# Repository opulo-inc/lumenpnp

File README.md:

# LumenPnP

The LumenPnP is an open source [pick and place machine](https://en.wikipedia.org/wiki/Pick-and-place_machine) that reliably and accurately assembles electronic components onto circuit boards.

The LumenPnP is available for sale on the [Opulo Website](https://www.opulo.io/products/lumenpnp). Machines are being used in active production daily. If you build or buy one, please help the project by documenting bugs with a GitHub issue.

**Please [read the wiki here](https://github.com/opulo-inc/lumenpnp/wiki)!** The wiki covers information about the state of the project, contributing instructions, and frequently asked questions.

Along with the pick and place machine itself, the project also includes feeders designed to work with the machine. The source for powered feeders can be found [in their separate repository](https://github.com/opulo-inc/feeder).

For exported versions of the source (STLs, schematic PDFs, compiled binaries, etc), you can find them attached to the [latest release](https://github.com/opulo-inc/lumenpnp/releases).

The LumenPnP's development process is being cataloged in a series of videos. A playlist of these can be found [here](https://www.youtube.com/playlist?list=PLIeJXmcg1baLBz3x0nCDqkYpKs2IWGHk4).

## How do I get one?

You can buy a machine on the [Opulo Website](https://www.opulo.io/products/lumenpnp)!

## Contributing

If you would like to contribute to the project, awesome! Check out the [contributing page](https://github.com/opulo-inc/lumenpnp/wiki/Contributing) to get started.

## Community

Discussion about the project happens on the [LumenPnP Discord server](https://discordapp.com/invite/TCwy6De)!

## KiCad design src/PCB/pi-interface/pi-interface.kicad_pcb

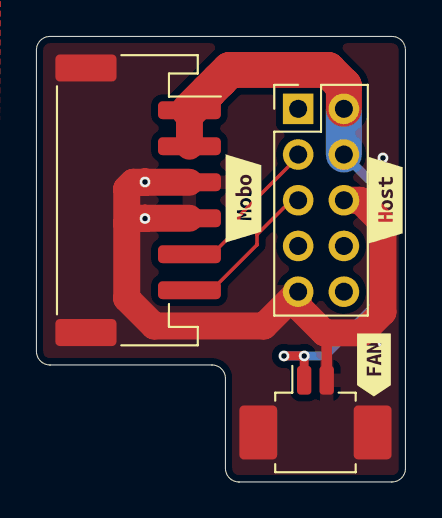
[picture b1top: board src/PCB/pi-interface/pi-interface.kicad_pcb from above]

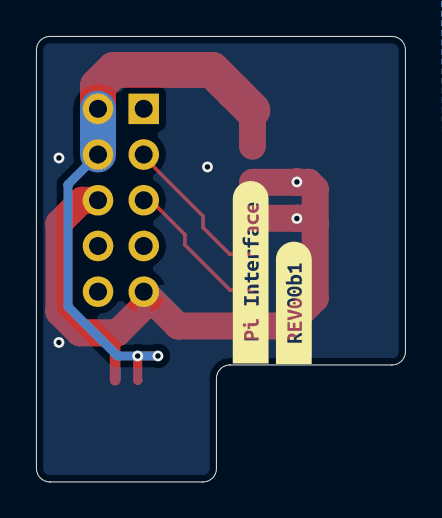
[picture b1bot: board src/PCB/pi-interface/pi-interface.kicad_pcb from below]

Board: 2 copper layers, 20.5 x 24.8 mm, 8 parts (2 on the bottom side), 4 nets.

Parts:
J1: PI; PinHeader_2x05_P2.54mm_Vertical
J2: MOBO; JST_PH_S6B-PH-SM4-TB_1x06-1MP_P2.00mm_Horizontal
J3: Conn_01x02_Pin; Molex_PicoBlade_53261-0271_1x02-1MP_P1.25mm_Horizontal
kibuzzard-6ABE9D80: G***; kibuzzard-6ABE9D80
kibuzzard-6ABE9DFF: G***; kibuzzard-6ABE9DFF
kibuzzard-6ABE9E4D: G***; kibuzzard-6ABE9E4D
kibuzzard-6ABE9E31: G***; kibuzzard-6ABE9E31
kibuzzard-6ABE9EAF: G***; kibuzzard-6ABE9EAF

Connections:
+5V: J1.2, J1.4, J2.1, J2.2, J3.1
BOOT: J1.3, J2.5
GND: J1.6, J1.9, J2.3, J2.4, J2.MP (MountPin), J3.2, J3.MP
RESET: J1.5, J2.6

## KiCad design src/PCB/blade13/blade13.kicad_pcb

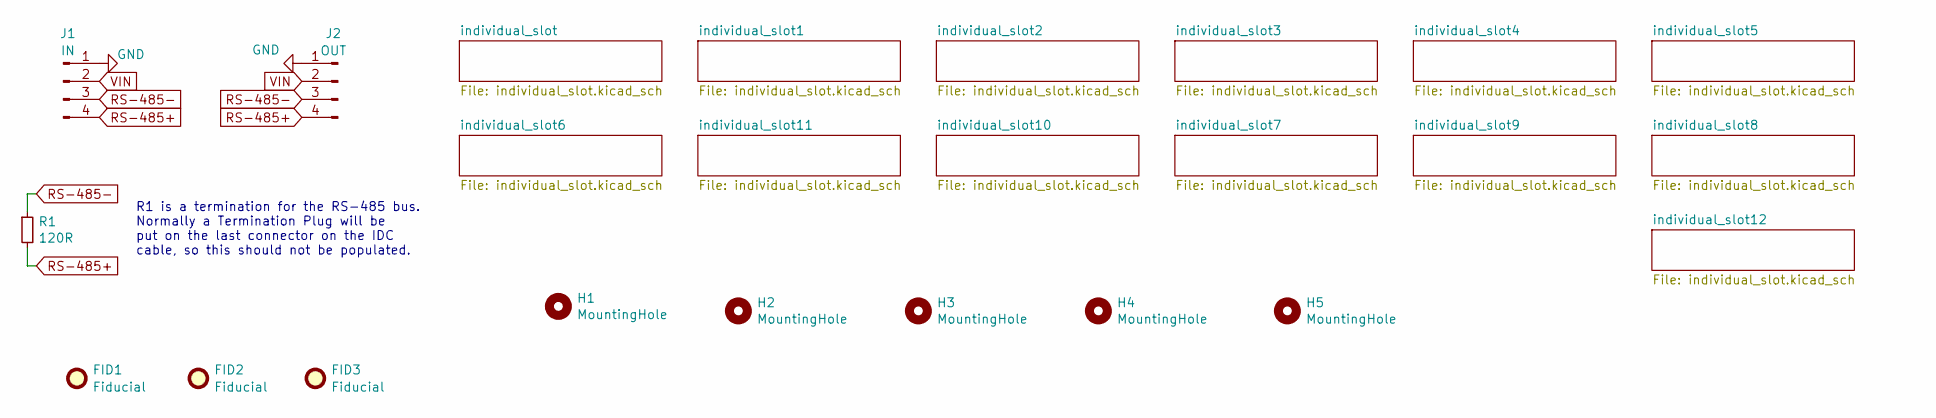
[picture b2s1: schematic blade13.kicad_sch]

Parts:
FID1, FID2, FID3: Fiducial; Fiducial_1mm_Mask2mm
H1, H2, H3, H4, H5: MountingHole; MountingHole_3.2mm_M3
J1: IN; JST_PH_B4B-PH-SM4-TB_1x04-1MP_P2.00mm_Vertical
J2: OUT; JST_PH_B4B-PH-SM4-TB_1x04-1MP_P2.00mm_Vertical
R1: 120R; R_0805_2012Metric; JLCPCB C17437

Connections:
GND: J1.1, J1.MP, J2.1, J2.MP; also elsewhere on the board
RS-485+: J1.4, J2.4, R1.2; also elsewhere on the board
RS-485-: J1.3, J2.3, R1.1; also elsewhere on the board
VIN: J1.2, J2.2; also elsewhere on the board

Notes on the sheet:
R1 is a termination for the RS-485 bus. Normally a Termination Plug will be put on the last connector on the IDC cable, so this should not be populated.

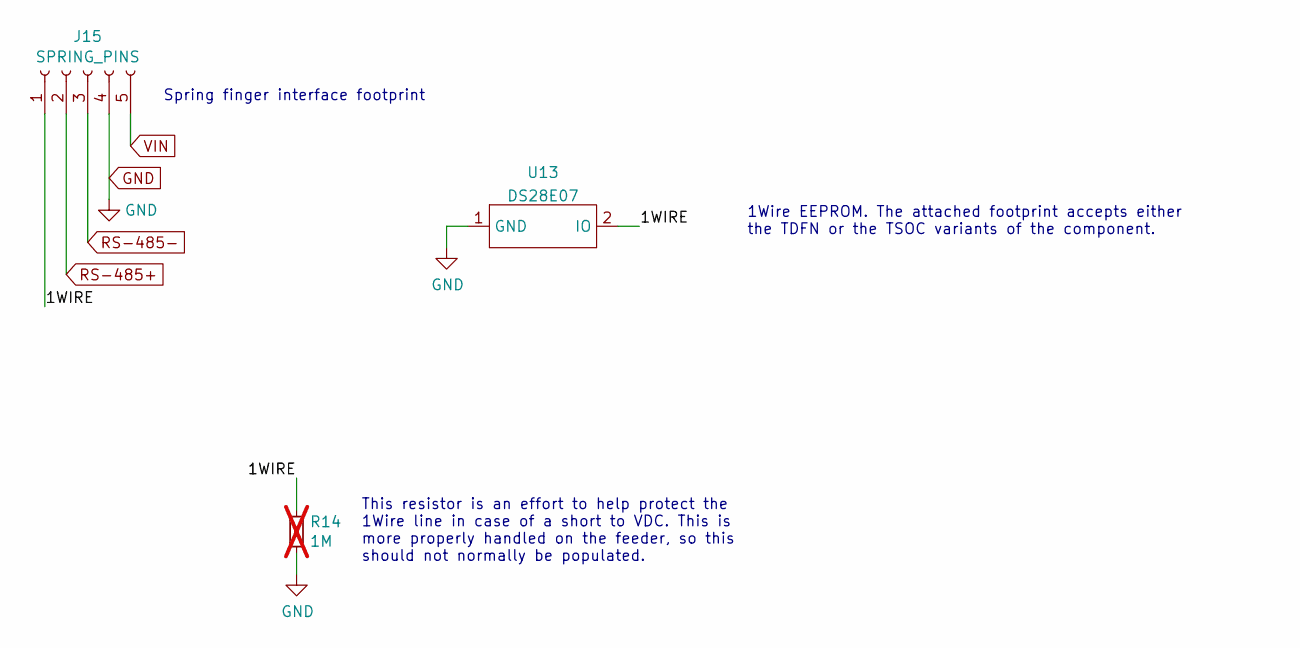
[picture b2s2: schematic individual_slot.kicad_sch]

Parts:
J15: SPRING_PINS; AVX-915-005-541-Contact-Surface
R14: 1M; R_0805_2012Metric; JLCPCB C17437; not fitted
U13: DS28E07; DS28E07_MULTI

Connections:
/individual_slot12/1WIRE: J15.1, R14.1, U13.2 (IO)
GND: J15.4, R14.2, U13.1 (GND); also elsewhere on the board
RS-485+: J15.2; also elsewhere on the board
RS-485-: J15.3; also elsewhere on the board
VIN: J15.5; also elsewhere on the board

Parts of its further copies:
J3, J4, J5, J6, J7, J8, J9, J10, J11, J12, J13, J14: SPRING_PINS; AVX-915-005-541-Contact-Surface
R2, R3, R4, R5, R6, R7, R8, R9, R10, R11, R12, R13: 1M; R_0805_2012Metric; JLCPCB C17437; not fitted
U1, U2, U3, U4, U5, U6, U7, U8, U9, U10, U11, U12: DS28E07; DS28E07_MULTI

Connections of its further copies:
/individual_slot1/1WIRE: J4.1, R3.1, U2.2 (IO)
/individual_slot2/1WIRE: J5.1, R4.1, U3.2 (IO)
/individual_slot3/1WIRE: J6.1, R5.1, U4.2 (IO)
/individual_slot4/1WIRE: J7.1, R6.1, U5.2 (IO)
/individual_slot5/1WIRE: J8.1, R7.1, U6.2 (IO)
/individual_slot6/1WIRE: J9.1, R8.1, U7.2 (IO)
/individual_slot7/1WIRE: J10.1, R9.1, U8.2 (IO)
/individual_slot8/1WIRE: J11.1, R10.1, U9.2 (IO)
/individual_slot9/1WIRE: J12.1, R11.1, U10.2 (IO)
/individual_slot10/1WIRE: J13.1, R12.1, U11.2 (IO)
/individual_slot11/1WIRE: J14.1, R13.1, U12.2 (IO)
/individual_slot/1WIRE: J3.1, R2.1, U1.2 (IO)
GND: J3.4, J4.4, J5.4, J6.4, J7.4, J8.4, J9.4, J10.4, J11.4, J12.4, J13.4, J14.4, R2.2, R3.2, R4.2, R5.2, R6.2, R7.2, R8.2, R9.2, R10.2, R11.2, R12.2, R13.2, U1.1 (GND), U2.1 (GND), U3.1 (GND), U4.1 (GND), U5.1 (GND), U6.1 (GND), U7.1 (GND), U8.1 (GND), U9.1 (GND), U10.1 (GND), U11.1 (GND), U12.1 (GND); also elsewhere on the board
RS-485+: J3.2, J4.2, J5.2, J6.2, J7.2, J8.2, J9.2, J10.2, J11.2, J12.2, J13.2, J14.2; also elsewhere on the board
RS-485-: J3.3, J4.3, J5.3, J6.3, J7.3, J8.3, J9.3, J10.3, J11.3, J12.3, J13.3, J14.3; also elsewhere on the board
VIN: J3.5, J4.5, J5.5, J6.5, J7.5, J8.5, J9.5, J10.5, J11.5, J12.5, J13.5, J14.5; also elsewhere on the board

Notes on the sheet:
This resistor is an effort to help protect the 1Wire line in case of a short to VDC. This is more properly handled on the feeder, so this should not normally be populated.
Spring finger interface footprint
1Wire EEPROM. The attached footprint accepts either the TDFN or the TSOC variants of the component.

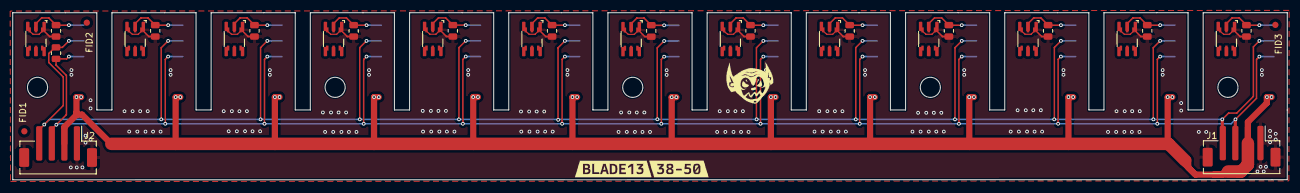
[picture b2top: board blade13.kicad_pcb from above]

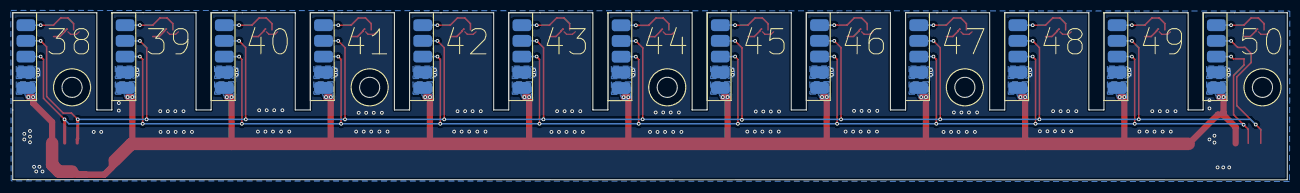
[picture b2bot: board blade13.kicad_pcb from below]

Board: 2 copper layers, 203.0 x 26.6 mm, 53 parts (13 on the bottom side), 17 nets.

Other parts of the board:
kibuzzard-65FDDA45: G***; kibuzzard-65FDDA45
kibuzzard-65FDDA59: G***; kibuzzard-65FDDA59
kibuzzard-65FDDA61: G***; kibuzzard-65FDDA61

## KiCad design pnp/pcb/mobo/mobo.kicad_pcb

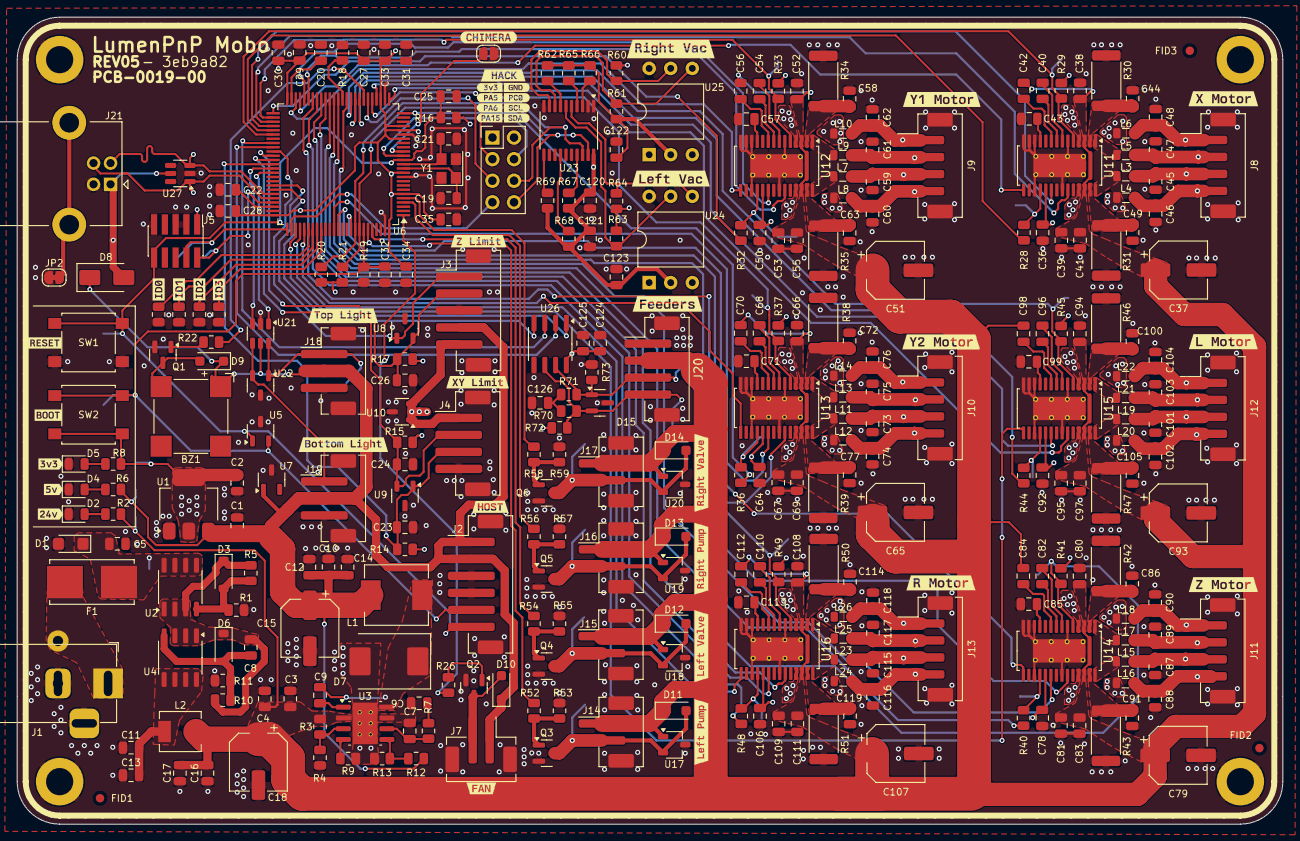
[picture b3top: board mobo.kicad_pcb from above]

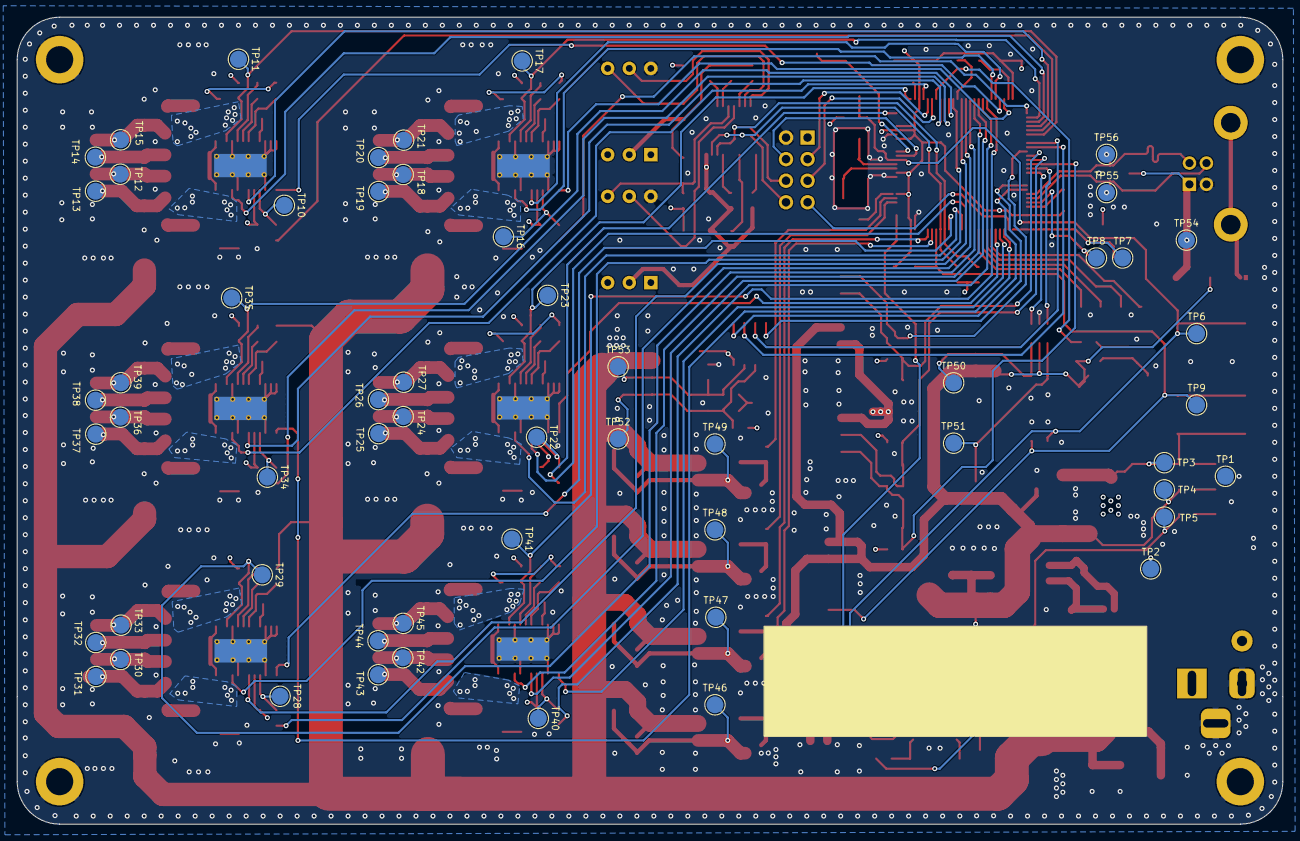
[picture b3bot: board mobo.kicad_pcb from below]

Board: 4 copper layers, 149.0 x 95.0 mm, 404 parts (57 on the bottom side), 207 nets.

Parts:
BZ1: Buzzer; MagneticBuzzer_CUI_CMT-8504-100-SMT
C1, C2, C3, C4, C5, C10, C11, C12, C13, C14, C16, C17, C38, C52, C66, C80, C94, C108, C121: 10u; C_0805_2012Metric
C6: 4.7n; C_0805_2012Metric
C7: 47p; C_0805_2012Metric
C8, C9, C23, C24, C25, C26, C29, C30, C31, C32, C33, C34, C35, C36, C39, C41, C42, C44, C49, C50, C53, C55, C56, C58, C63, C64, C67, C69, C70, C72, C77, C78, C81, C83, C84, C86, C91, C92, C95, C97, C98, C100, C105, C106, C109, C111, C112, C114, C119, C120, C122, C123, C124, C125, C126: 100n; C_0805_2012Metric
C15, C18, C37, C51, C65, C79, C93, C107: 100u; CP_Elec_6.3x7.7
C19, C21: 10p; C_0805_2012Metric
C20, C22, C27, C28: 2.2u; C_0805_2012Metric
C40, C54, C68, C82, C96, C110: 22n; C_0805_2012Metric
C43, C57, C71, C85, C99, C113: 4.7u; C_0805_2012Metric
C45, C46, C47, C48, C59, C60, C61, C62, C73, C74, C75, C76, C87, C88, C89, C90, C101, C102, C103, C104, C115, C116, C117, C118: 470p; C_0805_2012Metric
D1: SMF28A; D_SMF
D2, D4, D5: Green; LED_0805_2012Metric
D3, D6: BZT52C16; D_SOD-123
D7: B560C; D_SMC
D8: SS34; D_SMA
D9, D10, D11, D12, D13, D14: SM4007; D_SOD-123F
D15: SM712_SOT23; SOT-23
F1: Fuse; Fuseholder_Littelfuse_Nano2_154x
FID1, FID2, FID3: Fiducial; Fiducial_1mm_Mask2mm
G1: Opulo-Logo; logo_mask
G2: Goblin-logo; goblin
H1, H2, H3, H4: MountingHole_Pad; MountingHole_3.2mm_M3_DIN965_Pad
J1: COMBO_POWER_JACK; BarrelJack_Horizontal
J2: HOST; JST_PH_B6B-PH-SM4-TB_1x06-1MP_P2.00mm_Vertical
J3: Z_LIMIT; JST_PH_B5B-PH-SM4-TB_1x05-1MP_P2.00mm_Vertical
J4: XY_LIMIT; JST_PH_B4B-PH-SM4-TB_1x04-1MP_P2.00mm_Vertical
J5: SWD Header; PinHeader_2x05_P1.27mm_Vertical_SMD
J6: HACK_HEADER; PinHeader_2x04_P2.54mm_Vertical
J7: FAN; JST_PH_B2B-PH-SM4-TB_1x02-1MP_P2.00mm_Vertical
J8, J9, J10, J11, J12, J13: MOTOR; JST_PH_B4B-PH-SM4-TB_1x04-1MP_P2.00mm_Vertical
J14, J15, J16, J17: FET; JST_PH_B2B-PH-SM4-TB_1x02-1MP_P2.00mm_Vertical
J18: TOP_LIGHT; JST_PH_B3B-PH-SM4-TB_1x03-1MP_P2.00mm_Vertical
J19: BTM_LIGHT; JST_PH_B3B-PH-SM4-TB_1x03-1MP_P2.00mm_Vertical
J20: FEEDERS; JST_PH_B4B-PH-SM4-TB_1x04-1MP_P2.00mm_Vertical
J21: USB_B; USB_B_Lumberg_2411_02_Horizontal
JP1: CHIMERA_JUMPER; SolderJumper-2_P1.3mm_Open_RoundedPad1.0x1.5mm
JP2: SHIELD_GND; SolderJumper-2_P1.3mm_Bridged_RoundedPad1.0x1.5mm
L1: 8.2uH; L_Sunlord_MWSA0603S
L2: 2.2u; L_Sunlord_MWSA0402S
L3, L4, L5, L6, L7, L8, L9, L10, L11, L12, L13, L14, L15, L16, L17, L18, L19, L20, L21, L22, L23, L24, L25, L26: L_Ferrite; L_0805_2012Metric
Q1, Q2, Q3, Q4, Q5, Q6: AO3400A; SOT-23
R1, R2, R3, R11, R13, R14, R15, R16, R17, R18, R19, R29, R33, R37, R41, R45, R49, R53, R55, R57, R59, R62, R65, R66, R67, R68, R69: 10k; R_0805_2012Metric
R4, R5, R6, R10, R20, R21, R60, R61, R63, R64: 4.7k; R_0805_2012Metric
R7: 16.9k; R_0805_2012Metric
R8, R22, R26, R28, R32, R36, R40, R44, R48, R52, R54, R56, R58: 1k; R_0805_2012Metric
R9: 243k; R_0805_2012Metric
R12: 53.6k; R_0805_2012Metric
R23, R24, R25, R27: 0R; R_0805_2012Metric
R30, R31, R34, R35, R38, R39, R42, R43, R46, R47, R50, R51: 120m; R_2512_6332Metric
R70, R71: 60.4; R_0805_2012Metric
R72, R73: 330; R_0805_2012Metric
SW1, SW2: SW_Push; SW_SPST_B3S-1000
TP1, TP2, TP3, TP4, TP5, TP6, TP7, TP8, TP9, TP10, TP11, TP12, TP13, TP14, TP15, TP16, TP17, TP18, TP19, TP20, TP21, TP22, TP23, TP24, TP25, TP26, TP27, TP28, TP29, TP30, TP31, TP32, TP33, TP34, TP35, TP36, TP37, TP38, TP39, TP40, TP41, TP42, TP43, TP44, TP45, TP46, TP47, TP48, TP49, TP50, TP51, TP52, TP53, TP54, TP55, TP56: TestPoint; TestPoint_Pad_D2.0mm
U1: AP1117-33; SOT-223-3_TabPin2
U2, U4: FDS4435BZ; SO-8_3.9x4.9mm_P1.27mm
U3: TPS54560BDDA; Texas_R-PDSO-G8_EP2.95x4.9mm_Mask2.4x3.1mm_ThermalVias
U5, U8, U9, U10: PESD3V3S2UT; SOT-23-3
U6: STM32F407VETx; LQFP-100_14x14mm_P0.5mm
U7, U22: PESD5V2S2UT; SOT-23-3
U11, U12, U13, U14, U15, U16: TMC2226-SA; HTSSOP-28-1EP_4.4x9.7mm_P0.65mm_EP2.75x6.2mm_ThermalVias
U17, U18, U19, U20: PESD24BS3; TSOT-23
U21: SN74LVC2G34; SOT-23-6
U23: PCA9545A; TSSOP-20_4.4x6.5mm_P0.65mm
U24, U25: XGZP6857D; DIP-6_W10.16mm
U26: THVD1400D; SOIC-8_3.9x4.9mm_P1.27mm
U27: SRV05-4; SOT-23-6
Y1: 8MHz; Crystal_SMD_3225-4Pin_3.2x2.5mm
kibuzzard-65DCF286: G***; kibuzzard-65DCF286
kibuzzard-65E24FAE: G***; kibuzzard-65E24FAE
kibuzzard-65E215D8: G***; kibuzzard-65E215D8
kibuzzard-65E215EC: G***; kibuzzard-65E215EC
kibuzzard-65E240B2: G***; kibuzzard-65E240B2
kibuzzard-65E241C9: G***; kibuzzard-65E241C9
kibuzzard-65E2151D: G***; kibuzzard-65E2151D
kibuzzard-65E2155B: G***; kibuzzard-65E2155B
kibuzzard-65E2156F: G***; kibuzzard-65E2156F
kibuzzard-65E2408C: G***; kibuzzard-65E2408C
kibuzzard-65E2409D: G***; kibuzzard-65E2409D
kibuzzard-65E2504F: G***; kibuzzard-65E2504F
kibuzzard-65E24108: G***; kibuzzard-65E24108
kibuzzard-65E24112: G***; kibuzzard-65E24112
kibuzzard-65E24141: G***; kibuzzard-65E24141
kibuzzard-65E25035: G***; kibuzzard-65E25035
kibuzzard-65E25071: G***; kibuzzard-65E25071
kibuzzard-65F1FEA3: G***; kibuzzard-65F1FEA3
kibuzzard-6585C0AF: G***; kibuzzard-6585C0AF
kibuzzard-6585C0D3: G***; kibuzzard-6585C0D3
kibuzzard-6585C08F: G***; kibuzzard-6585C08F
kibuzzard-6585C058: G***; kibuzzard-6585C058
kibuzzard-6606EA2E: G***; kibuzzard-6606EA2E
kibuzzard-6606EA4F: G***; kibuzzard-6606EA4F
kibuzzard-6606EA6E: G***; kibuzzard-6606EA6E
kibuzzard-65709CC6: G***; kibuzzard-65709CC6
kibuzzard-65709E62: G***; kibuzzard-65709E62
kibuzzard-65848E86: G***; kibuzzard-65848E86
kibuzzard-65848E91: G***; kibuzzard-65848E91
kibuzzard-65848EB6: G***; kibuzzard-65848EB6
kibuzzard-65848FCC: G***; kibuzzard-65848FCC
kibuzzard-65848FD5: G***; kibuzzard-65848FD5
kibuzzard-65848FDC: G***; kibuzzard-65848FDC
kibuzzard-65848FE3: G***; kibuzzard-65848FE3
kibuzzard-65848FE9: G***; kibuzzard-65848FE9
kibuzzard-65848FEF: G***; kibuzzard-65848FEF
kibuzzard-660711AC: G***; kibuzzard-660711AC
kibuzzard-66071149: G***; kibuzzard-66071149

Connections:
+3.3V: C2.1, C27.1, C28.1, C29.1, C30.1, C31.1, C33.1, C34.1, C35.1, C36.2, C50.2, C64.2, C78.2, C92.2, C106.2, C120.1, C121.1, C122.1, C123.1, C124.1, C125.1, J3.5, J4.1, J5.1 (VTref), J6.1, R8.1, R14.2, R15.2, R16.1, R17.2, R20.1, R21.1, R29.1, R33.1, R37.1, R41.1, R45.1, R49.1, R60.2, R61.2, R62.1, R63.1, R64.1, R65.1, R66.1, R67.2, R68.2, R69.2, R72.1, SW2.2, TP3.1 (1_1), U1.2 (VO), U6.6 (VBAT), U6.11 (VDD), U6.19 (VDD), U6.21 (VREF+), U6.22 (VDDA), U6.28 (VDD), U6.50 (VDD), U6.75 (VDD), U6.100 (VDD), U10.1, U10.2, U11.19 (VCC_IO), U12.19 (VCC_IO), U13.19 (VCC_IO), U14.19 (VCC_IO), U15.19 (VCC_IO), U16.19 (VCC_IO), U23.20 (VDD), U24.2 (VDD), U25.2 (VDD), U26.8 (VCC)
+5V: BZ1.1 (-), C1.1, C10.2, C12.2, C14.2, C15.1, D8.1 (K), D9.1 (K), D10.1 (K), J2.1, J2.2, J3.4, J7.1, J18.2, J19.2, L1.2, R6.1, R12.1, TP4.1 (1_1), U1.3 (VI), U7.1, U21.5 (VCC)
/Lighting/BTM_LIGHT: U6.64 (PC7), U21.3 (2A)
/Microcontroller/AUX: J3.1, U6.60 (PD13), U8.1
/Microcontroller/BOOT1: R18.1, U6.37 (PB2)
/Microcontroller/BUZZER: R22.1, U6.32 (PA7)
/Microcontroller/CHIMERA: JP1.1 (A), U6.16 (PC1)
/Microcontroller/FAN: R26.1, U6.1 (PE2)
/Microcontroller/I2C_SCL: J6.6, R20.2, U6.92 (PB6), U23.18 (SCL)
/Microcontroller/I2C_SDA: J6.8, R21.2, U6.93 (PB7), U23.19 (SDA)
/Microcontroller/ID0: R23.2, U6.81 (PD0)
/Microcontroller/ID1: R24.2, U6.82 (PD1)
/Microcontroller/ID2: R25.2, U6.83 (PD2)
/Microcontroller/ID3: R27.2, U6.84 (PD3)
/Microcontroller/LUMEN_AUX_A1: J6.4, U6.15 (PC0)
/Microcontroller/LUMEN_AUX_PWM1: J6.3, U6.30 (PA5)
/Microcontroller/LUMEN_AUX_PWM2: J6.5, U6.31 (PA6)
/Microcontroller/LUMEN_AUX_PWM3: J6.7, U6.77 (PA15)
/Microcontroller/MOS1: R52.2, U6.95 (PB8)
/Microcontroller/MOS2: R54.2, U6.96 (PB9)
/Microcontroller/MOS3: R56.2, U6.4 (PE5)
/Microcontroller/MOS4: R58.2, U6.5 (PE6)
/Microcontroller/PA2: R36.2, U6.25 (PA2)
/Microcontroller/PA3: R37.2, TP23.1 (1_1), U6.26 (PA3), U13.5 (~EN)
/Microcontroller/PA4: U6.29 (PA4), U15.23 (DIR)
/Microcontroller/PB0: R45.2, TP35.1 (1_1), U6.35 (PB0), U15.5 (~EN)
/Microcontroller/PB1: U6.36 (PB1), U14.23 (DIR)
/Microcontroller/PB5: U6.91 (PB5), U14.15 (DIAG)
/Microcontroller/PB10: U6.47 (PB10), U11.15 (DIAG)
/Microcontroller/PB11: U6.48 (PB11), U12.15 (DIAG)
/Microcontroller/PB12: R32.2, U6.51 (PB12)
/Microcontroller/PB13: R33.2, TP17.1 (1_1), U6.52 (PB13), U12.5 (~EN)
/Microcontroller/PB14: U6.53 (PB14), U11.23 (DIR)
/Microcontroller/PB15: U6.54 (PB15), U11.20 (STEP)
/Microcontroller/PC4: U6.33 (PC4), U15.20 (STEP)
/Microcontroller/PC5: R44.2, U6.34 (PC5)
/Microcontroller/PC10: U6.78 (PC10), U15.15 (DIAG)
/Microcontroller/PC11: U6.79 (PC11), U16.15 (DIAG)
/Microcontroller/PC12: U6.80 (PC12), U13.15 (DIAG)
/Microcontroller/PD6: U6.87 (PD6), U13.20 (STEP)
/Microcontroller/PD7: U6.88 (PD7), U13.23 (DIR)
/Microcontroller/PD9: R29.2, TP11.1 (1_1), U6.56 (PD9), U11.5 (~EN)
/Microcontroller/PE7: U6.38 (PE7), U14.20 (STEP)
/Microcontroller/PE8: R40.2, U6.39 (PE8)
/Microcontroller/PE9: R41.2, TP29.1 (1_1), U6.40 (PE9), U14.5 (~EN)
/Microcontroller/PE10: U6.41 (PE10), U16.23 (DIR)
/Microcontroller/PE11: U6.42 (PE11), U16.20 (STEP)
/Microcontroller/PE12: R48.2, U6.43 (PE12)
/Microcontroller/PE13: R49.2, TP41.1 (1_1), U6.44 (PE13), U16.5 (~EN)
/Microcontroller/PE14: U6.45 (PE14), U12.23 (DIR)
/Microcontroller/PE15: U6.46 (PE15), U12.20 (STEP)
/Microcontroller/RS485_DE: U6.58 (PD11), U26.3 (DE)
/Microcontroller/RS485_RE: U6.59 (PD12), U26.2 (~RE)
/Microcontroller/RS485_RX: U6.69 (PA10), U26.1 (RO)
/Microcontroller/RS485_TX: U6.68 (PA9), U26.4 (DI)
/Microcontroller/SWCLK: J5.4 (SWDCLK/TCK), TP7.1 (1_1), U6.76 (PA14)
/Microcontroller/SWDIO: J5.2 (SWDIO/TMS), TP8.1 (1_1), U6.72 (PA13)
/Microcontroller/USB_D+: J21.3 (D+), TP55.1 (1_1), U6.71 (PA12), U27.1 (IO1)
/Microcontroller/USB_D-: J21.2 (D-), TP56.1 (1_1), U6.70 (PA11), U27.3 (IO2)
/Microcontroller/X_LIMIT: C23.1, J4.3, R14.1, U6.63 (PC6), U9.1
/Microcontroller/X_UART: R28.2, U6.55 (PD8)
/Microcontroller/Y_LIMIT: C24.1, J4.2, R15.1, U6.62 (PD15), U9.2
/Microcontroller/Z_LIMIT: C26.1, J3.2, R17.1, U6.61 (PD14), U8.2
/Motor L/5VOUT: C99.2, U15.11 (5VOUT)
/Motor L/A1: C101.2, J12.3, L19.2, TP36.1 (1_1)
/Motor L/A2: C102.1, J12.4, L20.2, TP37.1 (1_1)
/Motor L/B1: C103.2, J12.2, L21.2, TP38.1 (1_1)
/Motor L/B2: C104.1, J12.1, L22.2, TP39.1 (1_1)
/Motor R/5VOUT: C113.2, U16.11 (5VOUT)
/Motor R/A1: C115.2, J13.3, L23.2, TP42.1 (1_1)
/Motor R/A2: C116.1, J13.4, L24.2, TP43.1 (1_1)
/Motor R/B1: C117.2, J13.2, L25.2, TP44.1 (1_1)
/Motor R/B2: C118.1, J13.1, L26.2, TP45.1 (1_1)
/Motor X/5VOUT: C43.2, U11.11 (5VOUT)
/Motor X/A1: C45.2, J8.3, L3.2, TP12.1 (1_1)
/Motor X/A2: C46.1, J8.4, L4.2, TP13.1 (1_1)
/Motor X/B1: C47.2, J8.2, L5.2, TP14.1 (1_1)
/Motor X/B2: C48.1, J8.1, L6.2, TP15.1 (1_1)
/Motor Y1/5VOUT: C57.2, U12.11 (5VOUT)
/Motor Y1/A1: C59.2, J9.3, L7.2, TP18.1 (1_1)
/Motor Y1/A2: C60.1, J9.4, L8.2, TP19.1 (1_1)
/Motor Y1/B1: C61.2, J9.2, L9.2, TP20.1 (1_1)
/Motor Y1/B2: C62.1, J9.1, L10.2, TP21.1 (1_1)
/Motor Y2/5VOUT: C71.2, U13.11 (5VOUT)
/Motor Y2/A1: C73.2, J10.3, L11.2, TP24.1 (1_1)
/Motor Y2/A2: C74.1, J10.4, L12.2, TP25.1 (1_1)
/Motor Y2/B1: C75.2, J10.2, L13.2, TP26.1 (1_1)
/Motor Y2/B2: C76.1, J10.1, L14.2, TP27.1 (1_1)
/Motor Z/5VOUT: C85.2, U14.11 (5VOUT)
/Motor Z/A1: C87.2, J11.3, L15.2, TP30.1 (1_1)
/Motor Z/A2: C88.1, J11.4, L16.2, TP31.1 (1_1)
/Motor Z/B1: C89.2, J11.2, L17.2, TP32.1 (1_1)
/Motor Z/B2: C90.1, J11.1, L18.2, TP33.1 (1_1)
/Power/POWER_SUPPLY: F1.1, J1.1, J1.4
/Power/VIN: C5.2, D1.1 (A1), F1.2, TP2.1 (1_1), U2.5 (D), U2.6 (D), U2.7 (D), U2.8 (D)
/RS485/RS-485+: D15.2 (A2), J20.4, R70.1, R72.2, TP52.1 (1_1), U26.6 (A)
/RS485/RS-485-: D15.1 (A1), J20.3, R71.2, R73.1, TP53.1 (1_1), U26.7 (B)
/Vacuum sensors/SC0: R63.2, U23.6 (SC0), U24.5 (SCL)
/Vacuum sensors/SC1: R60.1, U23.9 (SC1), U25.5 (SCL)
/Vacuum sensors/SD0: R64.2, U23.5 (SD0), U24.4 (SDA)
/Vacuum sensors/SD1: R61.1, U23.8 (SD1), U25.4 (SDA)
BOOT: C32.1, J2.5, R19.1, SW2.1, TP9.1 (1_1), U5.2, U6.94 (BOOT0)
GND: C1.2, C2.2, C3.1, C4.1, C5.1, C6.1, C7.1, C10.1, C11.1, C12.1, C13.1, C14.1, C15.2, C16.1, C17.1, C18.2, C19.2, C20.2, C21.2, C22.2, C23.2, C24.2, C25.2, C26.2, C27.2, C28.2, C29.2, C30.2, C31.2, C32.2, C33.2, C34.2, C35.2, C36.1, C37.2, C38.1, C39.1, C41.1, C43.1, C44.1, C45.1, C46.2, C47.1, C48.2, C49.1, C50.1, C51.2, C52.1, C53.1, C55.1, C57.1, C58.1, C59.1, C60.2, C61.1, C62.2, C63.1, C64.1, C65.2, C66.1, C67.1, C69.1, C71.1, C72.1, C73.1, C74.2, C75.1, C76.2, C77.1, C78.1, C79.2, C80.1, C81.1, C83.1, C85.1, C86.1, C87.1, C88.2, C89.1, C90.2, C91.1, C92.1, C93.2, C94.1, C95.1, C97.1, C99.1, C100.1, C101.1, C102.2, C103.1, C104.2, C105.1, C106.1, C107.2, C108.1, C109.1, C111.1, C113.1, C114.1, C115.1, C116.2, C117.1, C118.2, C119.1, C120.2, C121.2, C122.2, C123.2, C124.2, C125.2, C126.1, D1.2 (A2), D2.1 (K), D4.1 (K), D5.1 (K), D7.2 (A), D15.3 (common), H1.1 (1_1), H2.1 (1_1), H3.1 (1_1), H4.1 (1_1), J1.2, J1.3, J2.3, J2.4, J2.MP (MountPin), J3.3, J3.MP (MountPin), J4.4, J4.MP (MountPin), J5.3 (GND), J5.5 (GND), J5.9 (GNDDetect), J6.2, J7.MP (MountPin), J8.MP (MountPin), J9.MP (MountPin), J10.MP (MountPin), J11.MP (MountPin), J12.MP (MountPin), J13.MP (MountPin), J14.MP (MountPin), J15.MP (MountPin), J16.MP (MountPin), J17.MP (MountPin), J18.3, J18.MP (MountPin), J19.3, J19.MP (MountPin), J20.1, J20.MP (MountPin), J21.4 (GND), JP1.2 (B), JP2.2 (B), Q1.2 (S), Q2.2 (S), Q3.2 (S), Q4.2 (S), Q5.2 (S), Q6.2 (S), R1.2, R4.2, R9.2, R11.2, R13.2, R18.2, R19.2, R23.1, R24.1, R25.1, R27.1, R30.2, R31.2, R34.2, R35.2, R38.2, R39.2, R42.2, R43.2, R46.2, R47.2, R50.2, R51.2, R53.1, R55.1, R57.1, R59.1, R73.2, SW1.1, TP1.1 (1_1), U1.1 (GND), U3.7 (GND), U3.9 (GND), U5.3, U6.10 (VSS), U6.20 (VSSA), U6.27 (VSS), U6.74 (VSS), U6.99 (VSS), U7.3, U8.3, U9.3, U10.3, U11.6 (GND), U11.12 (MS1_AD0), U11.13 (NC), U11.14 (MS2_AD1), U11.17 (CLK), U11.22 (GND), U11.29 (GND), U12.6 (GND), U12.12 (MS1_AD0), U12.13 (NC), U12.14 (MS2_AD1), U12.17 (CLK), U12.22 (GND), U12.29 (GND), U13.6 (GND), U13.12 (MS1_AD0), U13.13 (NC), U13.14 (MS2_AD1), U13.17 (CLK), U13.22 (GND), U13.29 (GND), U14.6 (GND), U14.12 (MS1_AD0), U14.13 (NC), U14.14 (MS2_AD1), U14.17 (CLK), U14.22 (GND), U14.29 (GND), U15.6 (GND), U15.12 (MS1_AD0), U15.13 (NC), U15.14 (MS2_AD1), U15.17 (CLK), U15.22 (GND), U15.29 (GND), U16.6 (GND), U16.12 (MS1_AD0), U16.13 (NC), U16.14 (MS2_AD1), U16.17 (CLK), U16.22 (GND), U16.29 (GND), U17.3, U18.3, U19.3, U20.3, U21.2 (GND), U22.3, U23.1 (A0), U23.2 (A1), U23.10 (VSS), U24.6 (GND), U25.6 (GND), U26.5 (GND), U27.2 (VN), Y1.2, Y1.4
unnamed: BZ1.2 (+), D9.2 (A), Q1.3 (D)
unnamed: C6.2, R7.2
unnamed: C11.2, C13.2, L2.1, U4.5 (D), U4.6 (D), U4.7 (D), U4.8 (D)
unnamed: C126.2, R70.2, R71.1
unnamed: D2.2 (A), R2.2
unnamed: D3.2 (A), R1.1, R5.2, U2.4 (G)
unnamed: C8.2, D3.1 (K), D6.1 (K), R5.1, R10.1, U2.1 (S), U2.2 (S), U2.3 (S), U4.1 (S), U4.2 (S), U4.3 (S)
unnamed: D4.2 (A), R6.2
unnamed: D5.2 (A), R8.2
unnamed: C8.1, D6.2 (A), R10.2, R11.1, U4.4 (G)
unnamed: C9.1, D7.1 (K), L1.1, U3.8 (SW)
unnamed: D10.2 (A), J7.2, Q2.3 (D)
unnamed: D11.2 (A), J14.2, Q3.3 (D), TP46.1 (1_1), U17.2
unnamed: D12.2 (A), J15.2, Q4.3 (D), TP47.1 (1_1), U18.2
unnamed: D13.2 (A), J16.2, Q5.3 (D), TP48.1 (1_1), U19.2
unnamed: D14.2 (A), J17.2, Q6.3 (D), TP49.1 (1_1), U20.2
unnamed: J18.1, TP50.1 (1_1), U21.6 (1Y), U22.1
unnamed: J19.1, TP51.1 (1_1), U21.4 (2Y), U22.2
unnamed: J21.5 (Shield), JP2.1 (A)
unnamed: Q1.1 (G), R22.2
unnamed: Q2.1 (G), R26.2
unnamed: Q3.1 (G), R52.1, R53.2
unnamed: Q4.1 (G), R54.1, R55.2
unnamed: Q5.1 (G), R56.1, R57.2
unnamed: Q6.1 (G), R58.1, R59.2
unnamed: C9.2, U3.1 (BOOT)
unnamed: C7.2, R7.1, U3.6 (COMP)
unnamed: R3.2, R4.1, U3.3 (EN)
unnamed: R12.2, R13.1, U3.5 (FB)
unnamed: R9.1, U3.4 (RT/CLK)
unnamed: C19.1, U6.12 (PH0), Y1.1
unnamed: C21.1, U6.13 (PH1), Y1.3
unnamed: C20.1, U6.49 (VCAP_1)
unnamed: C22.1, U6.73 (VCAP_2)
unnamed: C49.2, R31.1, U11.27 (BRA)
unnamed: C44.2, R30.1, U11.2 (BRB)
unnamed: C40.2, U11.8 (CPI)
unnamed: C40.1, U11.7 (CPO)
unnamed: L3.1, U11.28 (OA1)
unnamed: L4.1, U11.25 (OA2)
unnamed: L5.1, U11.1 (OB1)
unnamed: L6.1, U11.4 (OB2)
unnamed: R28.1, TP10.1 (1_1), U11.18 (PDN_UART)
unnamed: C42.1, U11.9 (VCP)
unnamed: C63.2, R35.1, U12.27 (BRA)
unnamed: C58.2, R34.1, U12.2 (BRB)
unnamed: C54.2, U12.8 (CPI)
unnamed: C54.1, U12.7 (CPO)
unnamed: L7.1, U12.28 (OA1)
unnamed: L8.1, U12.25 (OA2)
unnamed: L9.1, U12.1 (OB1)
unnamed: L10.1, U12.4 (OB2)
unnamed: R32.1, TP16.1 (1_1), U12.18 (PDN_UART)
unnamed: C56.1, U12.9 (VCP)
unnamed: C77.2, R39.1, U13.27 (BRA)
unnamed: C72.2, R38.1, U13.2 (BRB)
unnamed: C68.2, U13.8 (CPI)
unnamed: C68.1, U13.7 (CPO)
unnamed: L11.1, U13.28 (OA1)
unnamed: L12.1, U13.25 (OA2)
unnamed: L13.1, U13.1 (OB1)
unnamed: L14.1, U13.4 (OB2)
unnamed: R36.1, TP22.1 (1_1), U13.18 (PDN_UART)
unnamed: C70.1, U13.9 (VCP)
unnamed: C91.2, R43.1, U14.27 (BRA)
unnamed: C86.2, R42.1, U14.2 (BRB)
unnamed: C82.2, U14.8 (CPI)
unnamed: C82.1, U14.7 (CPO)
unnamed: L15.1, U14.28 (OA1)
unnamed: L16.1, U14.25 (OA2)
unnamed: L17.1, U14.1 (OB1)
unnamed: L18.1, U14.4 (OB2)
unnamed: R40.1, TP28.1 (1_1), U14.18 (PDN_UART)
unnamed: C84.1, U14.9 (VCP)
unnamed: C105.2, R47.1, U15.27 (BRA)
unnamed: C100.2, R46.1, U15.2 (BRB)
unnamed: C96.2, U15.8 (CPI)
unnamed: C96.1, U15.7 (CPO)
unnamed: L19.1, U15.28 (OA1)
unnamed: L20.1, U15.25 (OA2)
unnamed: L21.1, U15.1 (OB1)
unnamed: L22.1, U15.4 (OB2)
unnamed: R44.1, TP34.1 (1_1), U15.18 (PDN_UART)
unnamed: C98.1, U15.9 (VCP)
unnamed: C119.2, R51.1, U16.27 (BRA)
unnamed: C114.2, R50.1, U16.2 (BRB)
unnamed: C110.2, U16.8 (CPI)
unnamed: C110.1, U16.7 (CPO)
unnamed: L23.1, U16.28 (OA1)
unnamed: L24.1, U16.25 (OA2)
unnamed: L25.1, U16.1 (OB1)
unnamed: L26.1, U16.4 (OB2)
unnamed: R48.1, TP40.1 (1_1), U16.18 (PDN_UART)
unnamed: C112.1, U16.9 (VCP)
unnamed: R65.2, U23.4 (_INT0_)
unnamed: R62.2, U23.7 (_INT1_)
unnamed: R69.1, U23.11 (_INT2_)
unnamed: R68.1, U23.14 (_INT3_)
unnamed: R67.1, U23.17 (_INT_)
unnamed: R66.2, U23.3 (_RESET_)
RESET: C25.1, J2.6, J5.10 (~RESET), R16.2, SW1.2, TP6.1 (1_1), U5.1, U6.14 (NRST)
TOP_LIGHT: U6.65 (PC8), U21.1 (1A)
VBUS: D8.2 (A), J21.1 (VBUS), TP54.1 (1_1), U27.5 (VP)
VDC: C3.2, C4.2, C16.2, C17.2, C18.1, C37.1, C38.2, C39.2, C41.2, C42.2, C51.1, C52.2, C53.2, C55.2, C56.2, C65.1, C66.2, C67.2, C69.2, C70.2, C79.1, C80.2, C81.2, C83.2, C84.2, C93.1, C94.2, C95.2, C97.2, C98.2, C107.1, C108.2, C109.2, C111.2, C112.2, D11.1 (K), D12.1 (K), D13.1 (K), D14.1 (K), J14.1, J15.1, J16.1, J17.1, J20.2, L2.2, R2.1, R3.1, TP5.1 (1_1), U3.2 (VIN), U11.3 (VS), U11.26 (VS), U12.3 (VS), U12.26 (VS), U13.3 (VS), U13.26 (VS), U14.3 (VS), U14.26 (VS), U15.3 (VS), U15.26 (VS), U16.3 (VS), U16.26 (VS), U17.1, U18.1, U19.1, U20.1

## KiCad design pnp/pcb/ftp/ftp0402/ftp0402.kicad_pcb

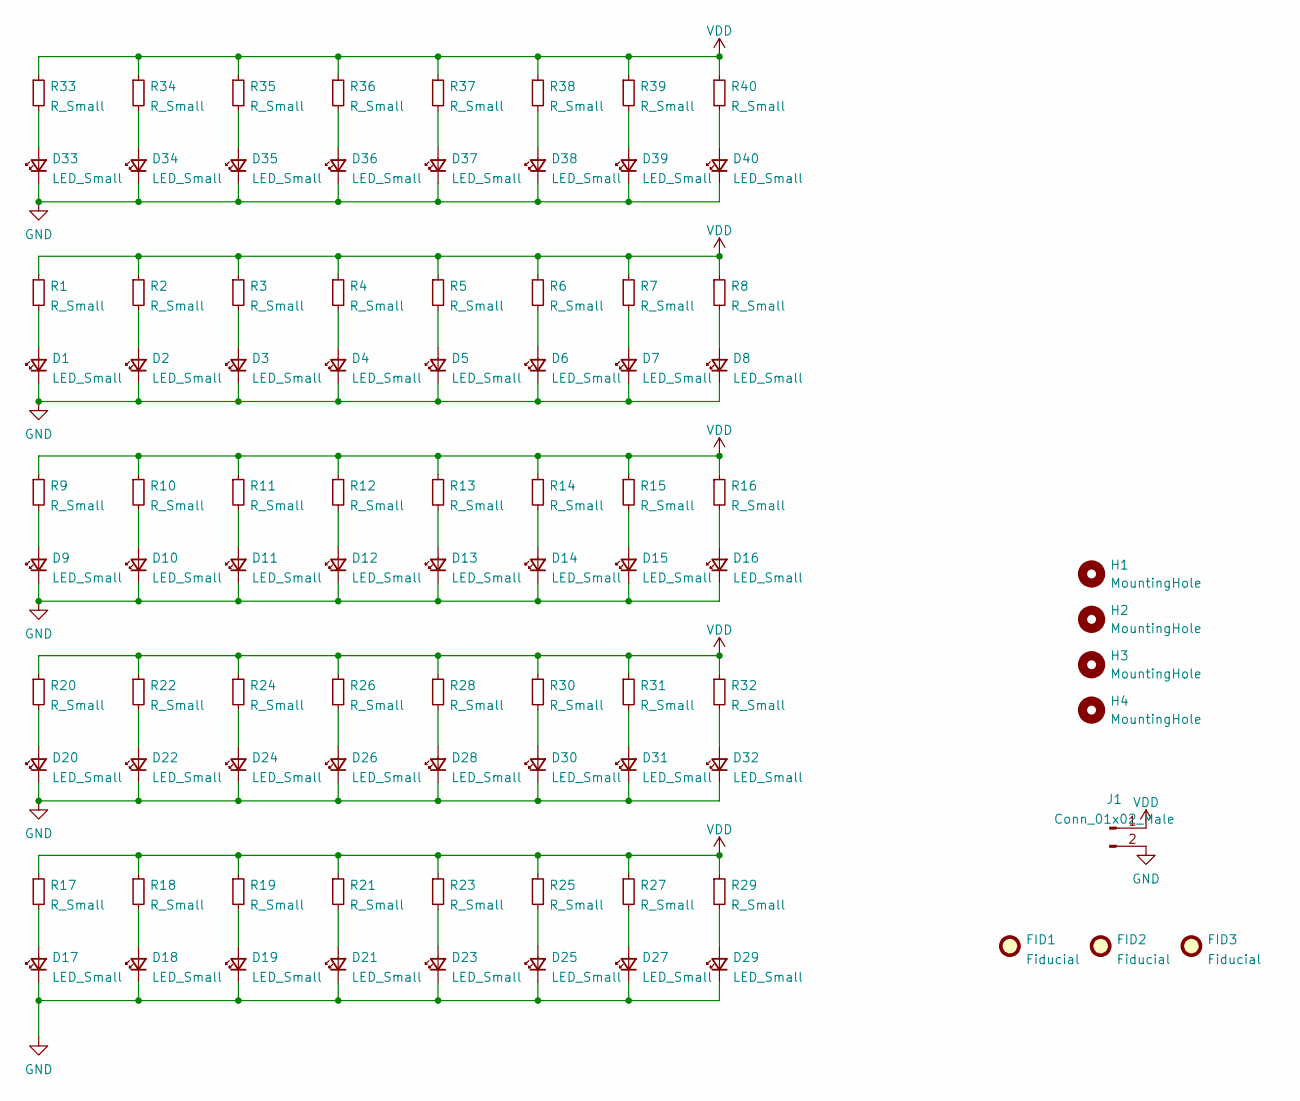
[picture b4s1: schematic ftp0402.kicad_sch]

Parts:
D1, D2, D3, D4, D5, D6, D7, D8, D9, D10, D11, D12, D13, D14, D15, D16, D17, D18, D19, D20, D21, D22, D23, D24, D25, D26, D27, D28, D29, D30, D31, D32, D33, D34, D35, D36, D37, D38, D39, D40: LED_Small; LED_0402_1005Metric
FID1, FID2, FID3: Fiducial; Fiducial_1mm_Mask3mm
H1, H2, H3, H4: MountingHole; MountingHole_3.2mm_M3_DIN965_Pad
J1: Conn_01x02_Male; PinHeader_1x02_P2.54mm_Vertical
R1, R2, R3, R4, R5, R6, R7, R8, R9, R10, R11, R12, R13, R14, R15, R16, R17, R18, R19, R20, R21, R22, R23, R24, R25, R26, R27, R28, R29, R30, R31, R32, R33, R34, R35, R36, R37, R38, R39, R40: R_Small; R_0402_1005Metric

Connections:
GND: D1.1 (K), D2.1 (K), D3.1 (K), D4.1 (K), D5.1 (K), D6.1 (K), D7.1 (K), D8.1 (K), D9.1 (K), D10.1 (K), D11.1 (K), D12.1 (K), D13.1 (K), D14.1 (K), D15.1 (K), D16.1 (K), D17.1 (K), D18.1 (K), D19.1 (K), D20.1 (K), D21.1 (K), D22.1 (K), D23.1 (K), D24.1 (K), D25.1 (K), D26.1 (K), D27.1 (K), D28.1 (K), D29.1 (K), D30.1 (K), D31.1 (K), D32.1 (K), D33.1 (K), D34.1 (K), D35.1 (K), D36.1 (K), D37.1 (K), D38.1 (K), D39.1 (K), D40.1 (K), J1.2
unnamed: D1.2 (A), R1.2
unnamed: D2.2 (A), R2.2
unnamed: D3.2 (A), R3.2
unnamed: D4.2 (A), R4.2
unnamed: D5.2 (A), R5.2
unnamed: D6.2 (A), R6.2
unnamed: D7.2 (A), R7.2
unnamed: D8.2 (A), R8.2
unnamed: D9.2 (A), R9.2
unnamed: D10.2 (A), R10.2
unnamed: D11.2 (A), R11.2
unnamed: D12.2 (A), R12.2
unnamed: D13.2 (A), R13.2
unnamed: D14.2 (A), R14.2
unnamed: D15.2 (A), R15.2
unnamed: D16.2 (A), R16.2
unnamed: D17.2 (A), R17.2
unnamed: D18.2 (A), R18.2
unnamed: D19.2 (A), R19.2
unnamed: D20.2 (A), R20.2
unnamed: D21.2 (A), R21.2
unnamed: D22.2 (A), R22.2
unnamed: D23.2 (A), R23.2
unnamed: D24.2 (A), R24.2
unnamed: D25.2 (A), R25.2
unnamed: D26.2 (A), R26.2
unnamed: D27.2 (A), R27.2
unnamed: D28.2 (A), R28.2
unnamed: D29.2 (A), R29.2
unnamed: D30.2 (A), R30.2
unnamed: D31.2 (A), R31.2
unnamed: D32.2 (A), R32.2
unnamed: D33.2 (A), R33.2
unnamed: D34.2 (A), R34.2
unnamed: D35.2 (A), R35.2
unnamed: D36.2 (A), R36.2
unnamed: D37.2 (A), R37.2
unnamed: D38.2 (A), R38.2
unnamed: D39.2 (A), R39.2
unnamed: D40.2 (A), R40.2
VDD: J1.1, R1.1, R2.1, R3.1, R4.1, R5.1, R6.1, R7.1, R8.1, R9.1, R10.1, R11.1, R12.1, R13.1, R14.1, R15.1, R16.1, R17.1, R18.1, R19.1, R20.1, R21.1, R22.1, R23.1, R24.1, R25.1, R26.1, R27.1, R28.1, R29.1, R30.1, R31.1, R32.1, R33.1, R34.1, R35.1, R36.1, R37.1, R38.1, R39.1, R40.1

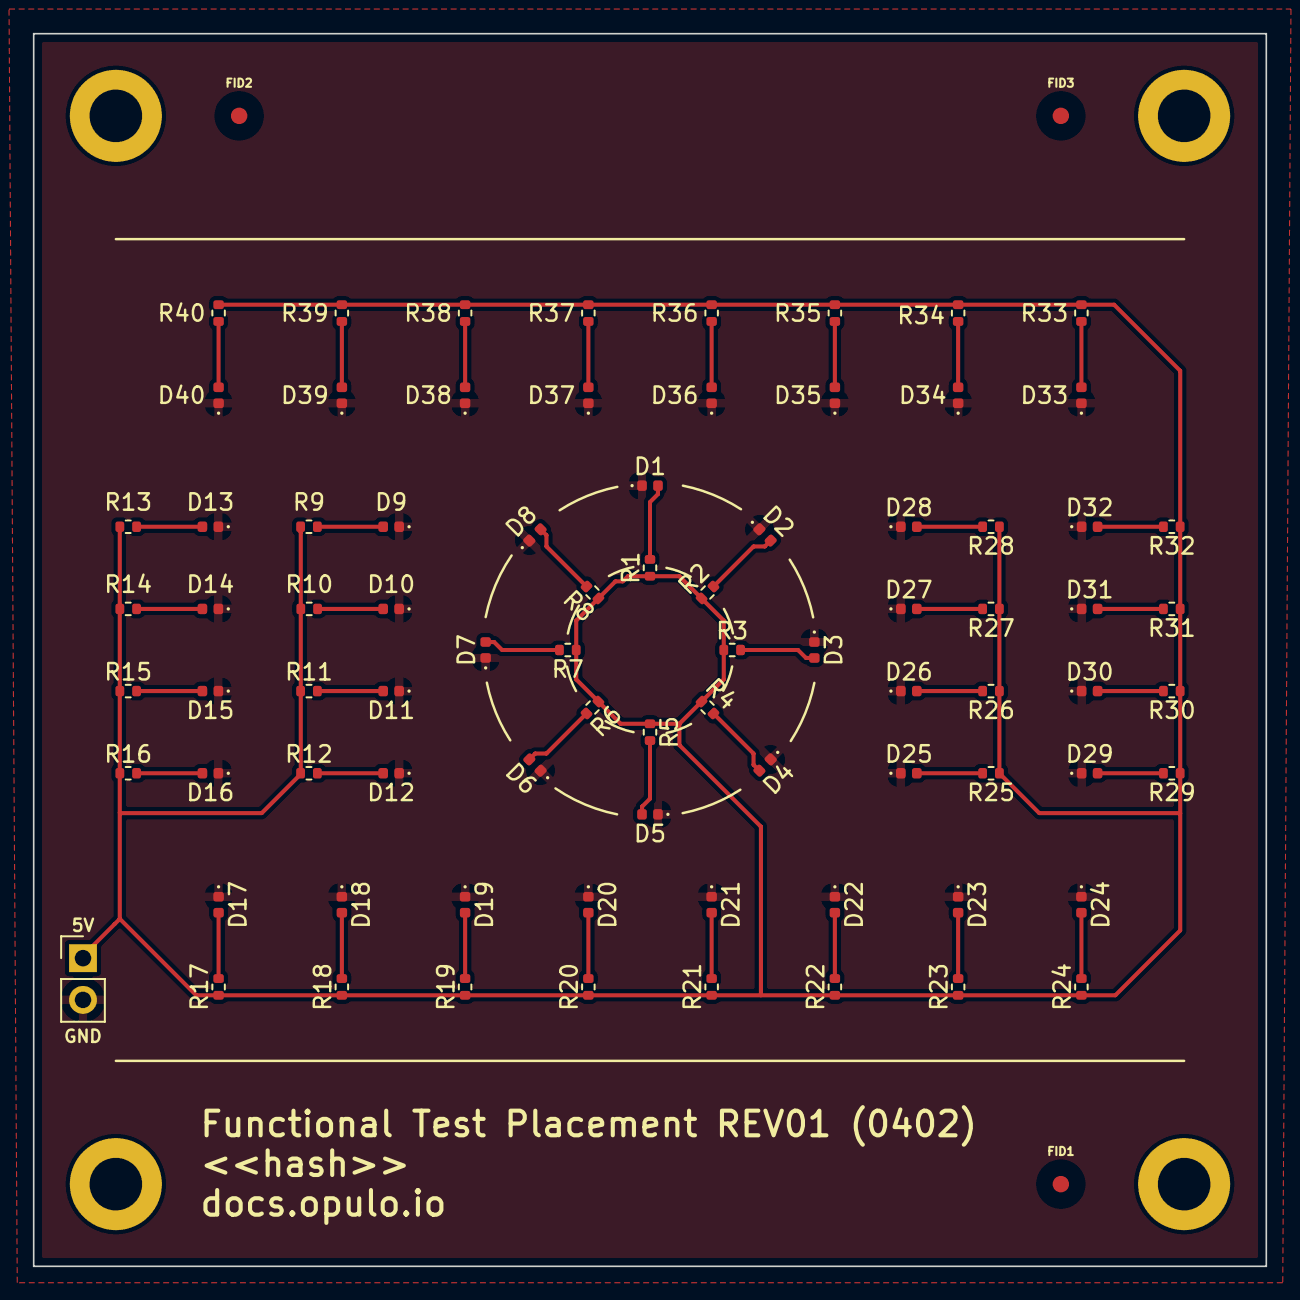
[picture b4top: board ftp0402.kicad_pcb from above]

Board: 2 copper layers, 75.0 x 75.0 mm, 90 parts (1 on the bottom side), 42 nets.

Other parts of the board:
G1: LOGO; opulo-logo
G2: LOGO; cal-dot-grid
